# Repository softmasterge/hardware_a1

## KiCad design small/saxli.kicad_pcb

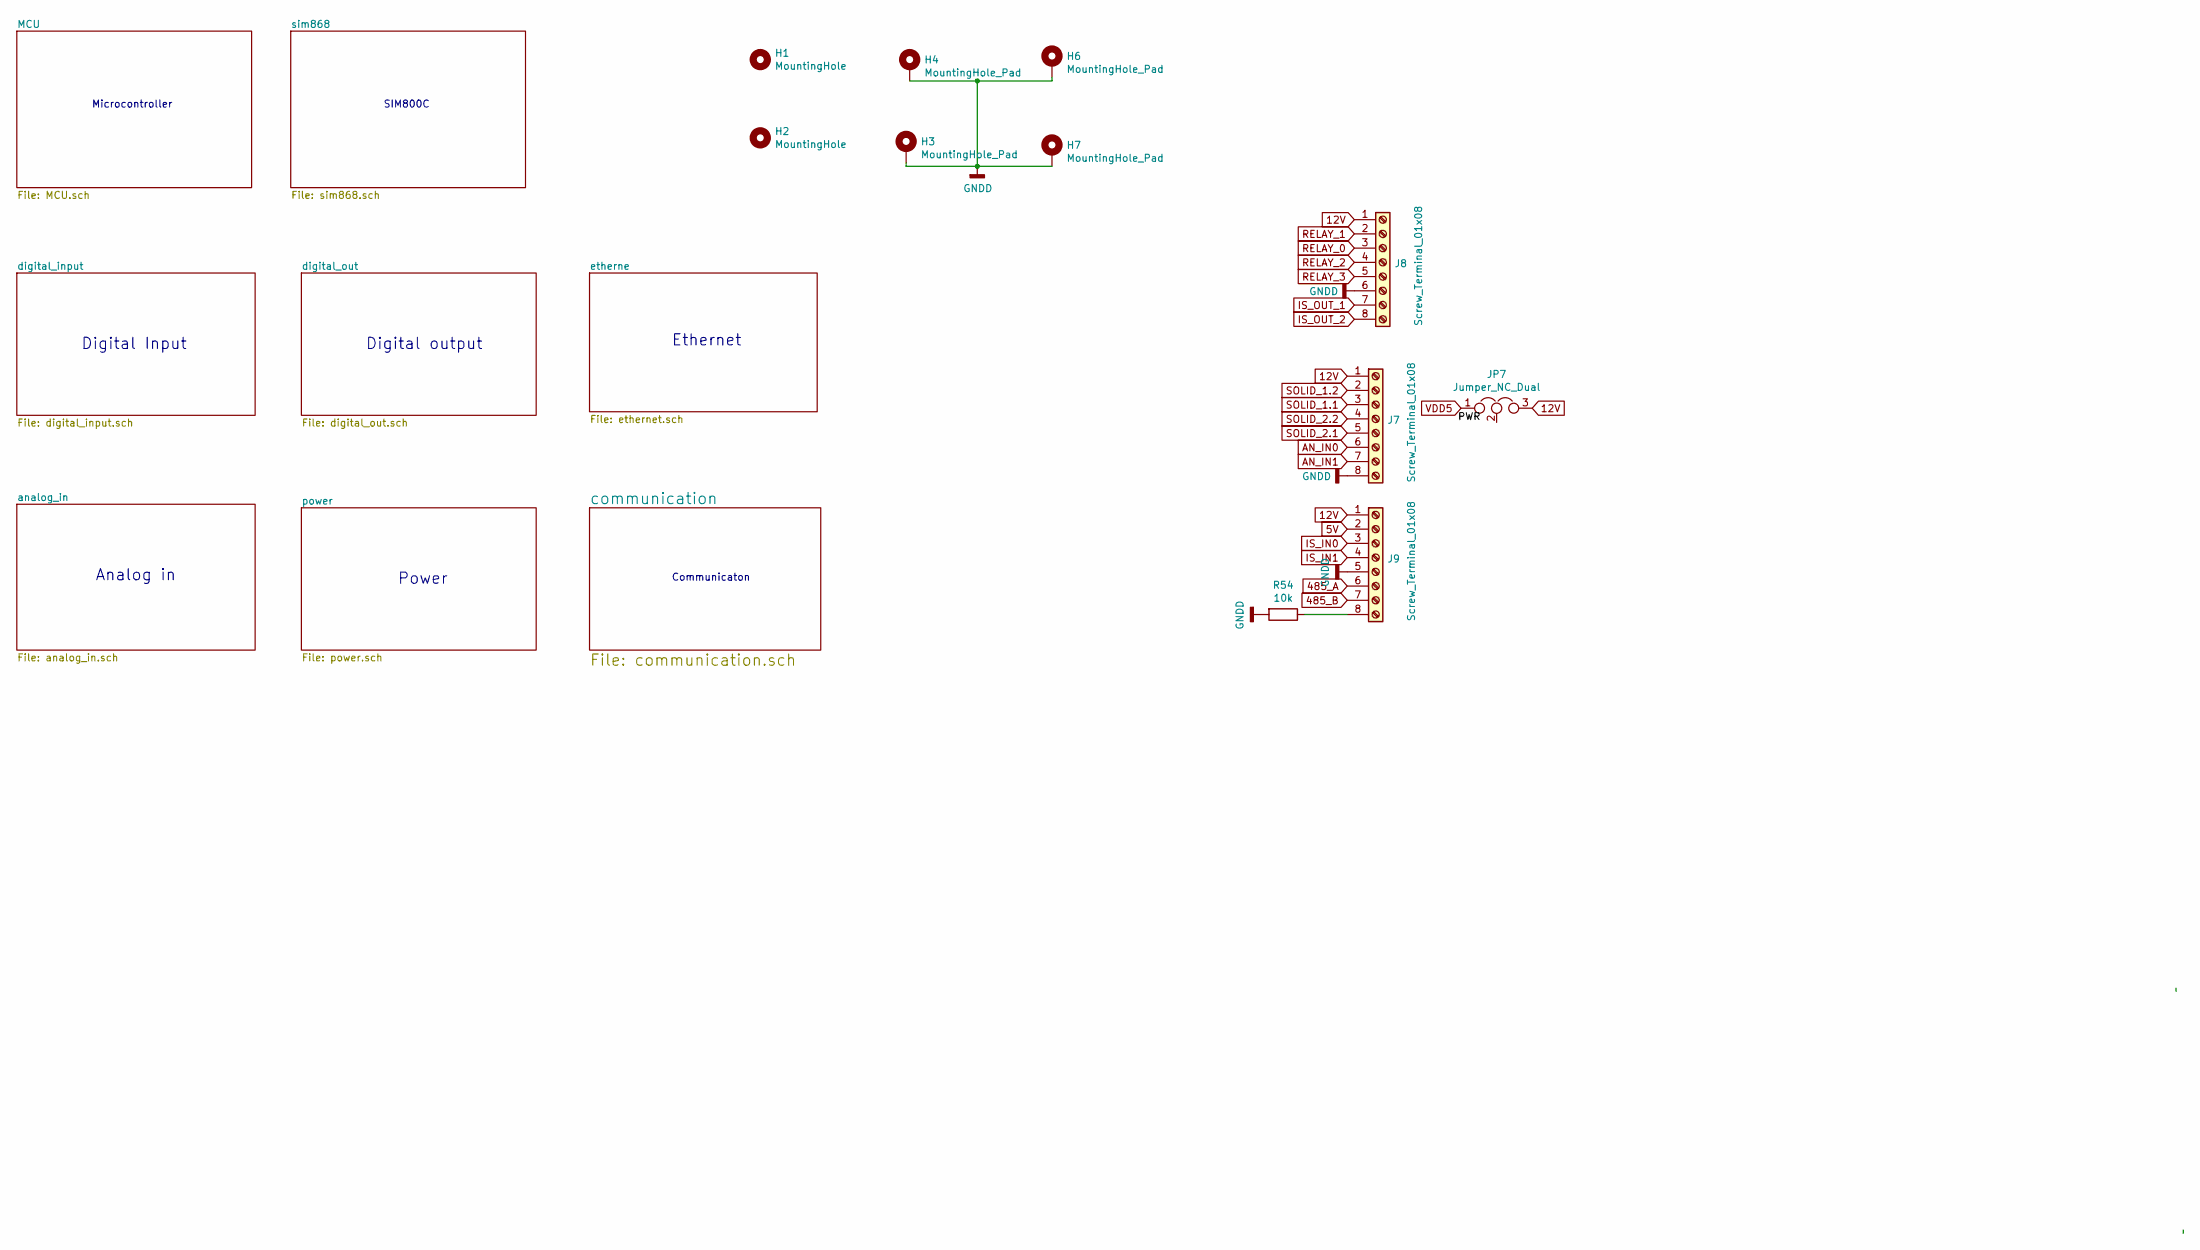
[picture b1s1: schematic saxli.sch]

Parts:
H1, H2: MountingHole; MountingHole_3.2mm_M3; LCSC N/A
H3, H4, H6, H7: MountingHole_Pad; MountingHole_3.2mm_M3_Pad; Mpn #; LCSC N/A
J7, J8, J9: Screw_Terminal_01x08; TerminalBlock_Phoenix_MPT-0,5-8-2.54_1x08_P2.54mm_Horizontal; LCSC N/A
JP7: Jumper_NC_Dual; SolderJumper-3_P1.3mm_Open_Pad1.0x1.5mm; LCSC N/A
R54: 10k; R_0603_1608Metric; MPN 0603WAF1002T5E; LCSC C25804

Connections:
5V: J9.2
485_A: J9.6; also elsewhere on the board
485_B: J9.7; also elsewhere on the board
AN_IN0: J7.6; also elsewhere on the board
AN_IN1: J7.7; also elsewhere on the board
GND: H3.1, H4.1, H6.1, H7.1, J7.8, J8.6, J9.5, R54.2; also elsewhere on the board
IS_IN0: J9.3; also elsewhere on the board
IS_IN1: J9.4; also elsewhere on the board
IS_OUT_1: J8.7; also elsewhere on the board
IS_OUT_2: J8.8; also elsewhere on the board
unnamed: J9.8, R54.1
RELAY_0: J8.3; also elsewhere on the board
RELAY_1: J8.2; also elsewhere on the board
RELAY_2: J8.4; also elsewhere on the board
RELAY_3: J8.5; also elsewhere on the board
SOLID_1.1: J7.3; also elsewhere on the board
SOLID_1.2: J7.2; also elsewhere on the board
SOLID_2.1: J7.5; also elsewhere on the board
SOLID_2.2: J7.4; also elsewhere on the board
VDD5: JP7.1; also elsewhere on the board

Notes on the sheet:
Microcontroller
Digital Input
Digital output
Ethernet
Analog in
Power
Communicaton
SIM800C

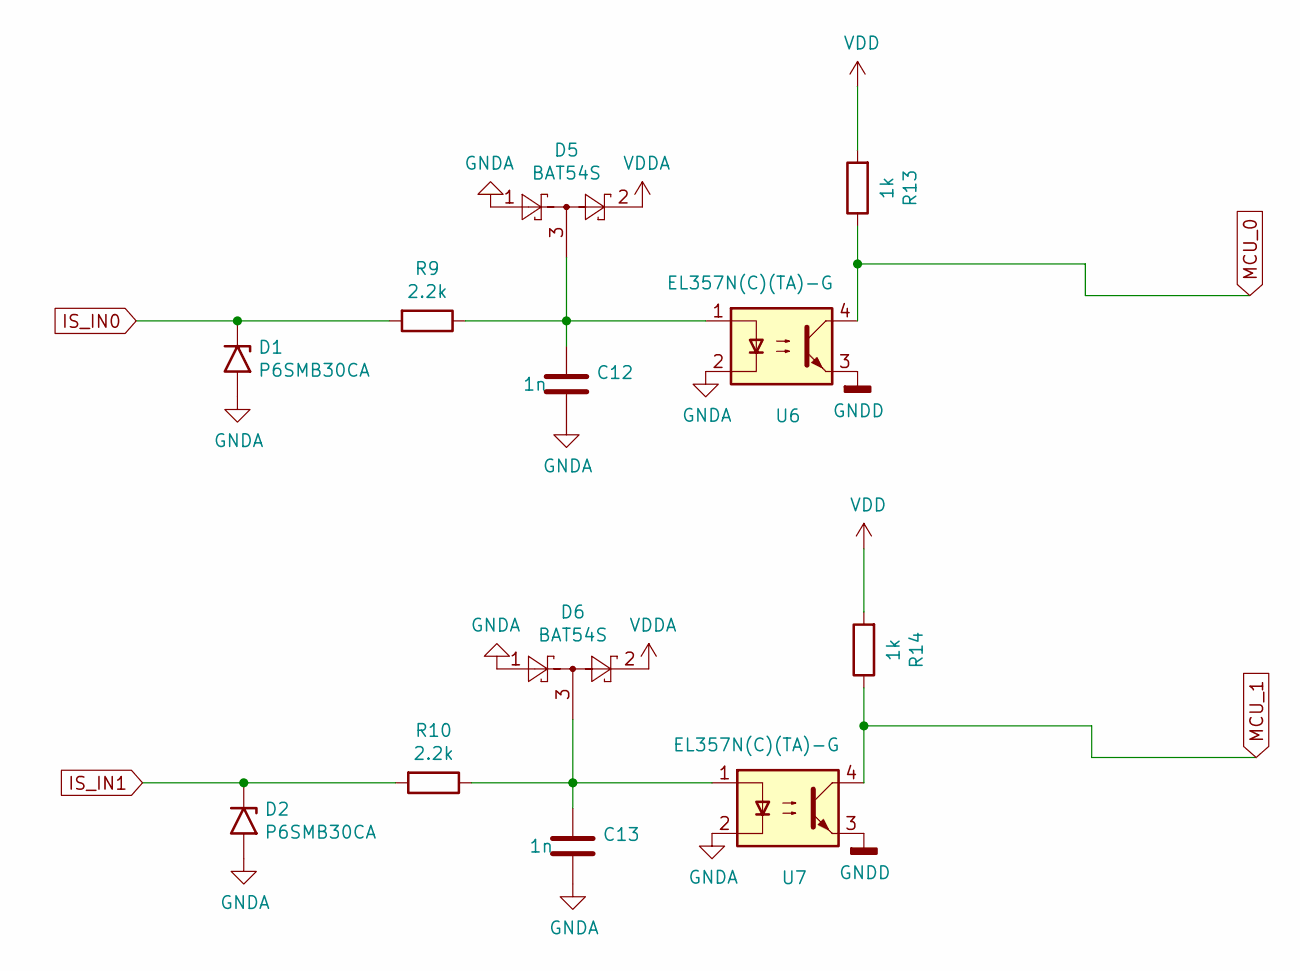
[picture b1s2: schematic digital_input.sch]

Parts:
C12, C13: 1n; C_0603_1608Metric; MPN CL21B102KBCNNNC; LCSC C46653
D1, D2: P6SMB30CA; D_SMB; MPN P6SMB30CA; LCSC C320521
D5, D6: BAT54S; SOT-23; MPN BAT54S L44; LCSC C122856
R9, R10: 2.2k; R_0805_2012Metric; MPN 0805W8F2201T5E; LCSC C17520
R13, R14: 1k; R_0805_2012Metric; MPN 0805W8F1001T5E; LCSC C17513
U6, U7: EL357N(C)(TA)-G; SO-4_4.4x3.6mm_P2.54mm; MPN EL357N(C)(TA)-G; LCSC C29981

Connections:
GND: C12.2, C13.2, D1.2 (A2), D2.2 (A2), D5.1, D6.1, U6.2, U6.3, U7.2, U7.3; also elsewhere on the board
IS_IN0: D1.1 (A1), R9.2; also elsewhere on the board
IS_IN1: D2.1 (A1), R10.2; also elsewhere on the board
MCU_0: R13.1, U6.4; also elsewhere on the board
MCU_1: R14.1, U7.4; also elsewhere on the board
unnamed: C12.1, D5.3, R9.1, U6.1
unnamed: C13.1, D6.3, R10.1, U7.1
VDD3: R13.2, R14.2; also elsewhere on the board
VDDA: D5.2, D6.2; also elsewhere on the board

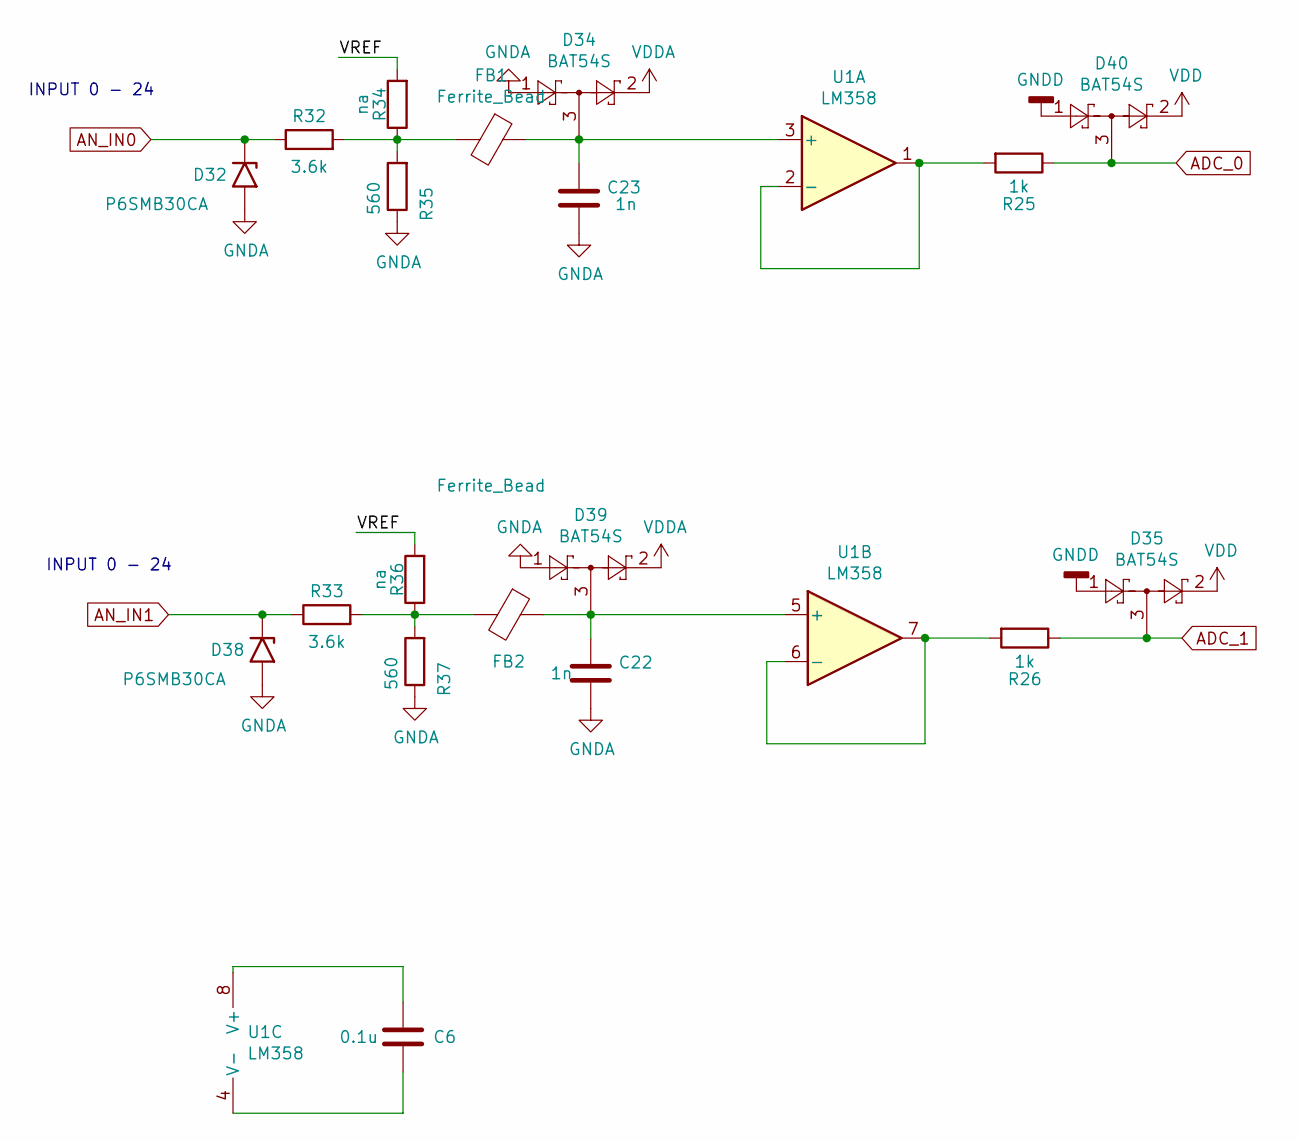
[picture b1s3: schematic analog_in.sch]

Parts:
C6: 0.1u; C_0603_1608Metric; MPN CC0603KRX7R9BB104; LCSC C14663
C22, C23: 1n; C_0603_1608Metric; MPN CL21B102KBCNNNC; LCSC C46653
D32, D38: P6SMB30CA; D_SMB; MPN P6SMB30CA; LCSC C320521
D34, D35, D39, D40: BAT54S; SOT-23; MPN BAT54S L44; LCSC C122856
FB1, FB2: Ferrite_Bead; R_0805_2012Metric_Pad1.20x1.40mm_HandSolder; MPN GZ2012D601TF; LCSC C1017
R25, R26: 1k; R_0603_1608Metric; MPN 0603WAF1001T5E; LCSC C21190
R32, R33: 3.6k; R_0805_2012Metric; MPN 0805W8F3601T5E; LCSC C18359
R34, R36: na; R_0603_1608Metric; LCSC N/A
R35, R37: 560; R_0805_2012Metric; MPN 0805W8F5600T5E; LCSC C28636
U1: LM358; SOIC-8_3.9x4.9mm_P1.27mm; LCSC C7950

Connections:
/analog_in/VREF: R34.2, R36.2
ADC_0: D40.3, R25.1; also elsewhere on the board
ADC_1: D35.3, R26.1; also elsewhere on the board
AN_IN0: D32.1 (A1), R32.1; also elsewhere on the board
AN_IN1: D38.1 (A1), R33.1; also elsewhere on the board
GND: C22.2, C23.2, D32.2 (A2), D34.1, D35.1, D38.2 (A2), D39.1, D40.1, R35.1, R37.1; also elsewhere on the board
unnamed: C6.1, U1.8 (V+)
unnamed: C6.2, U1.4 (V-)
unnamed: C22.1, D39.3, FB2.1, U1.5 (+)
unnamed: C23.1, D34.3, FB1.1, U1.3 (+)
unnamed: FB1.2, R32.2, R34.1, R35.2
unnamed: FB2.2, R33.2, R36.1, R37.2
unnamed: R25.2, U1.1, U1.2 (-)
unnamed: R26.2, U1.6 (-), U1.7
VDD3: D35.2, D40.2; also elsewhere on the board
VDDA: D34.2, D39.2; also elsewhere on the board

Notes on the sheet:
INPUT 0 - 24

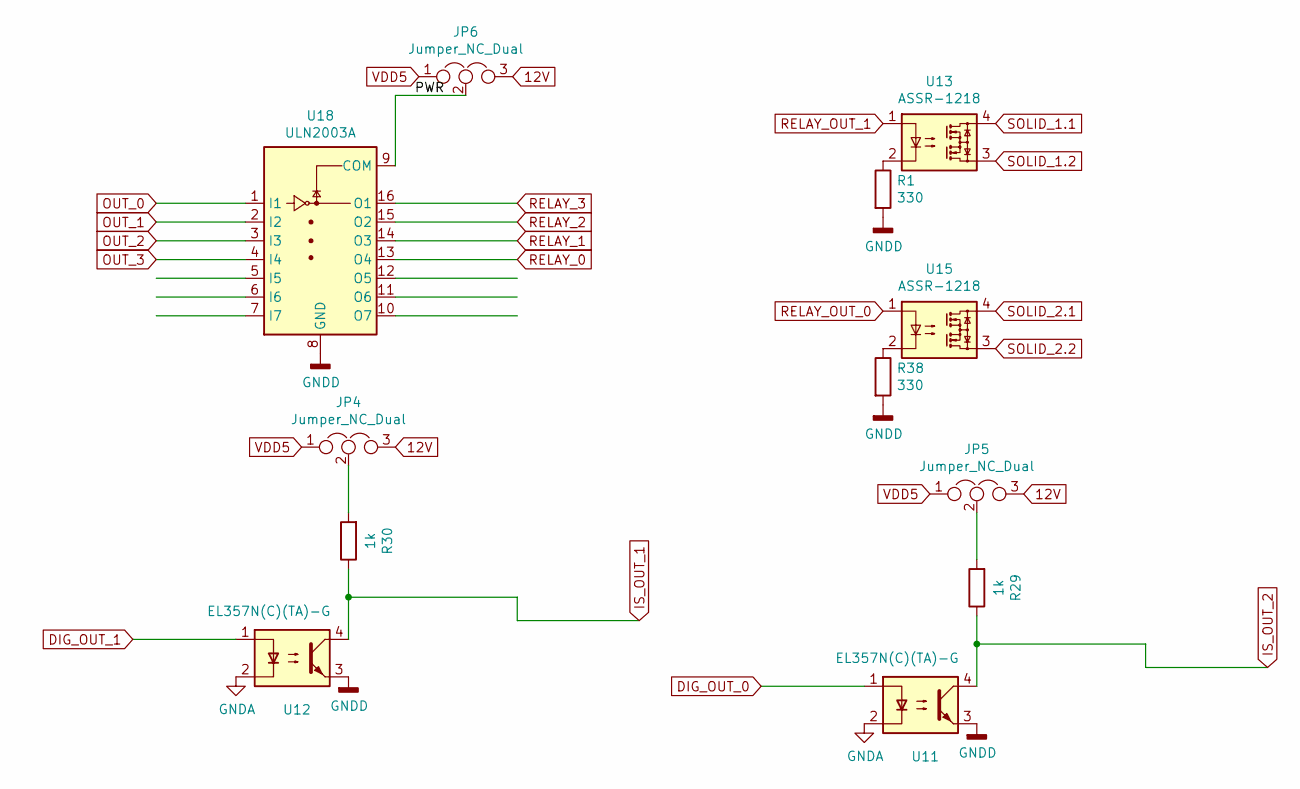
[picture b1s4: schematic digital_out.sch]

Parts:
JP4, JP5, JP6: Jumper_NC_Dual; SolderJumper-3_P1.3mm_Open_Pad1.0x1.5mm; LCSC N/A
R1, R38: 330; R_0603_1608Metric; MPN 0603WAF3300T5E; LCSC C23138
R29, R30: 1k; R_0805_2012Metric; MPN 0805W8F1001T5E; LCSC C17513
U11, U12: EL357N(C)(TA)-G; SO-4_4.4x3.6mm_P2.54mm; MPN EL357N(C)(TA)-G; LCSC C29981
U13, U15: ASSR-1218; SMDIP-4_W7.62mm; MPN AQY211EHAX; LCSC C129282
U18: ULN2003A; SOIC-16_3.9x9.9mm_P1.27mm; MPN ULN2003ADR; LCSC C7512

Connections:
/digital_out/PWR: JP6.2, U18.9 (COM)
DIG_OUT_0: U11.1; also elsewhere on the board
DIG_OUT_1: U12.1; also elsewhere on the board
GND: R1.2, R38.2, U11.2, U11.3, U12.2, U12.3, U18.8 (GND); also elsewhere on the board
IS_OUT_1: R30.1, U12.4; also elsewhere on the board
IS_OUT_2: R29.1, U11.4; also elsewhere on the board
unnamed: JP4.2, R30.2
unnamed: JP5.2, R29.2
unnamed: R1.1, U13.2
unnamed: R38.1, U15.2
OUT_0: U18.1 (I1); also elsewhere on the board
OUT_1: U18.2 (I2); also elsewhere on the board
OUT_2: U18.3 (I3); also elsewhere on the board
OUT_3: U18.4 (I4); also elsewhere on the board
RELAY_0: U18.13 (O4); also elsewhere on the board
RELAY_1: U18.14 (O3); also elsewhere on the board
RELAY_2: U18.15 (O2); also elsewhere on the board
RELAY_3: U18.16 (O1); also elsewhere on the board
RELAY_OUT_0: U15.1; also elsewhere on the board
RELAY_OUT_1: U13.1; also elsewhere on the board
SOLID_1.1: U13.4; also elsewhere on the board
SOLID_1.2: U13.3; also elsewhere on the board
SOLID_2.1: U15.4; also elsewhere on the board
SOLID_2.2: U15.3; also elsewhere on the board
VDD5: JP4.1, JP5.1, JP6.1; also elsewhere on the board

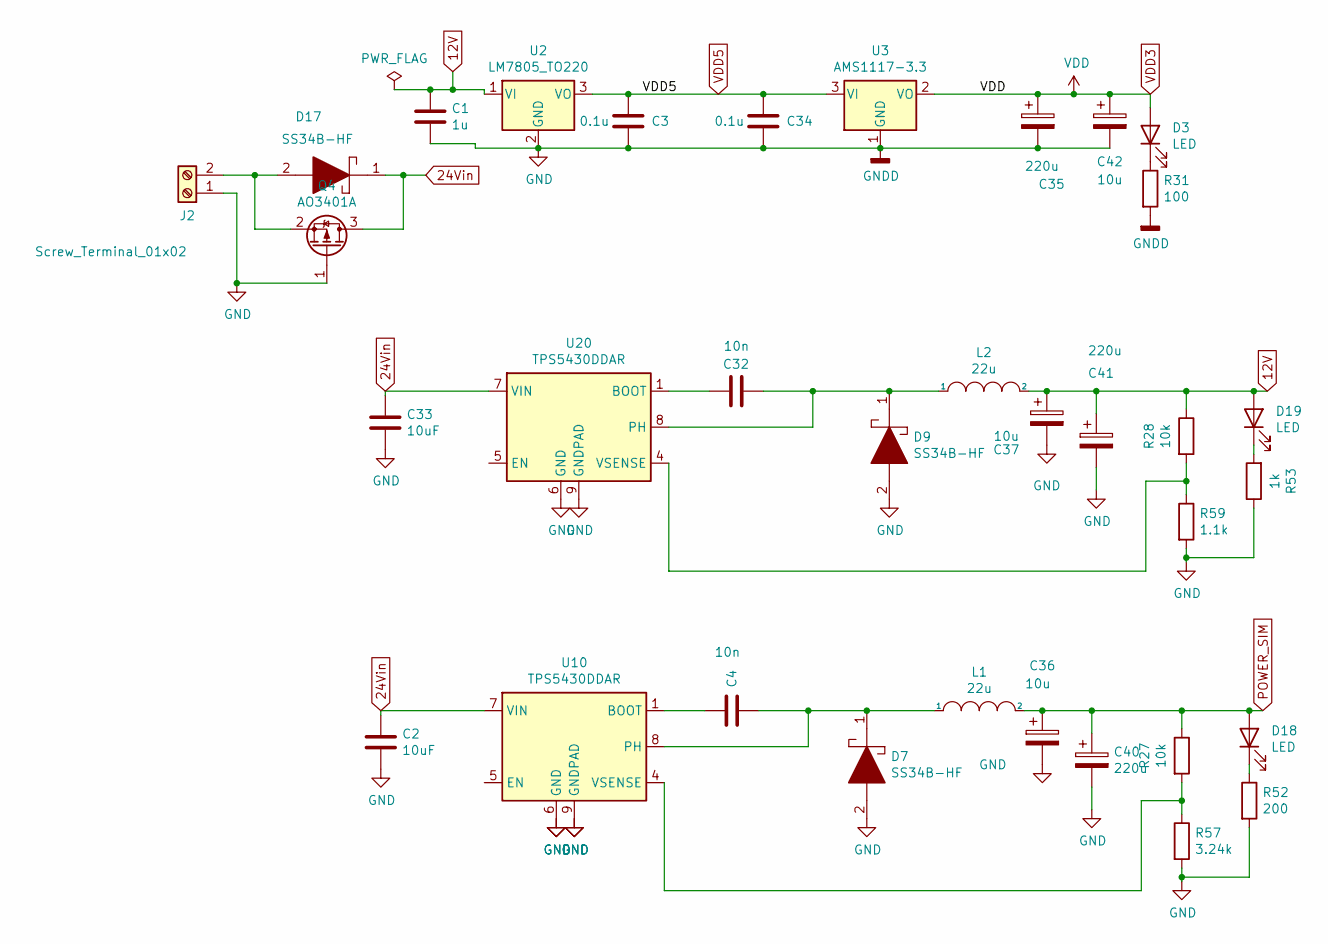
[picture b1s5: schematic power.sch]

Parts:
C1: 1u; R_0805_2012Metric; MPN CL21B105KBFNNNE; LCSC C28323
C2, C33: 10uF; C_1206_3216Metric; MPN CL31A106KBHNNNE; LCSC C13585
C3, C34: 0.1u; C_0603_1608Metric; MPN CC0603KRX7R9BB104; LCSC C14663
C4, C32: 10n; R_0603_1608Metric; MPN 0603B103K500NT; LCSC C57112
C35, C40, C41: 220u; CP_Elec_8x10; MPN VEH221M1VTR; LCSC C311611
C36, C37, C42: 10u; CP_EIA-3216-18_Kemet-A; MPN TAJA106K016RNJ; LCSC C7171
D3: LED; LED_0805_2012Metric; MPN FC-2012HRK-620D; LCSC C84256
D7, D9, D17: SS34B-HF; DIOM5336X320N; Mouser Part Number 750-SS34B-HF
D18, D19: LED; LED_0805_2012Metric_Pad1.15x1.40mm_HandSolder; MPN ORH-YG35A; LCSC C205449
J2: Screw_Terminal_01x02; TerminalBlock_Phoenix_MKDS-1,5-2-5.08_1x02_P5.08mm_Horizont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; Mpn Connector unknown; LCSC N/A
L1, L2: 22u; L_10.4x10.4_H4.8; MPN SLO1040H220MTT; LCSC C182173
Q4: AO3401A; SOT-23; MPN AO3401A; LCSC C15127
R27, R28: 10k; R_0603_1608Metric; MPN 0603WAF1002T5E; LCSC C25804
R31: 100; R_0603_1608Metric; MPN 0603WAF1000T5E; LCSC C22775
R52: 200; R_0603_1608Metric; MPN 0603WAF2000T5E; LCSC C8218
R53: 1k; R_0805_2012Metric; MPN 0805W8F1001T5E; LCSC C17513
R57: 3.24k; R_0603_1608Metric; MPN 0603WAF3241T5E; LCSC C22994
R59: 1.1k; R_0603_1608Metric; MPN 0603WAF1101T5E; LCSC C22764
U2: LM7805_TO220; TO-252-2; MPN CJ7805; LCSC C21706
U3: AMS1117-3.3; SOT-223; MPN AMS1117-3.3; LCSC C6186
U10, U20: TPS5430DDAR; TI_SO-PowerPAD-8_ThermalVias; MPN TPS5430DDAR; LCSC C9864

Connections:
24Vin: C2.1, C33.1, D17.1, Q4.3 (D), U10.7 (VIN), U20.7 (VIN)
GND: C1.2, C2.2, C3.2, C33.2, C34.2, C35.2, C36.2, C37.2, C40.2, C41.2, C42.2, D7.2, D9.2, J2.1, Q4.1 (G), R31.2, R52.2, R53.1, R57.2, R59.2, U2.2 (GND), U3.1 (GND), U10.6 (GND), U10.9 (GNDPAD), U20.6 (GND), U20.9 (GNDPAD); also elsewhere on the board
unnamed: C4.1, U10.1 (BOOT)
unnamed: C4.2, D7.1, L1.1, U10.8 (PH)
unnamed: C32.1, U20.1 (BOOT)
unnamed: C32.2, D9.1, L2.1, U20.8 (PH)
unnamed 72: C36.1, C40.1, D18.2 (A), L1.2, R27.1; also elsewhere on the board
unnamed: D3.1 (K), R31.1
unnamed: D17.2, J2.2, Q4.2 (S)
unnamed: D18.1 (K), R52.1
unnamed: D19.1 (K), R53.2
unnamed: R27.2, R57.1, U10.4 (VSENSE)
unnamed: R28.2, R59.1, U20.4 (VSENSE)
VDD3: C35.1, C42.1, D3.2 (A), U3.2 (VO); also elsewhere on the board
VDD5: C3.1, C34.1, U2.3 (VO), U3.3 (VI); also elsewhere on the board

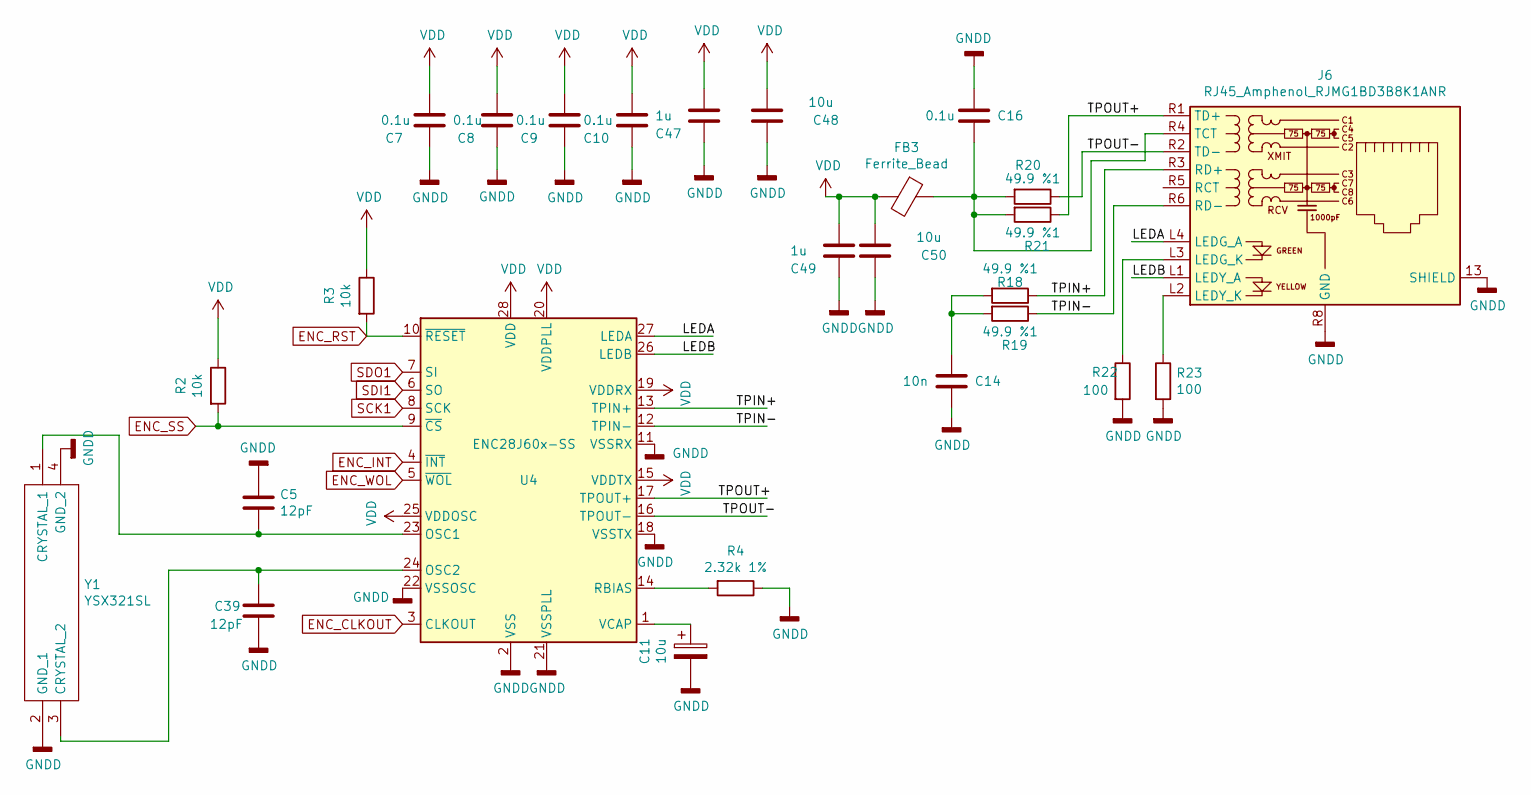
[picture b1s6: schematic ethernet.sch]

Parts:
C5, C39: 12pF; C_0603_1608Metric; MPN CL10C120JB8NNNC; LCSC C38523
C7, C8, C9, C10, C16: 0.1u; C_0603_1608Metric; MPN CC0603KRX7R9BB104; LCSC C14663
C11: 10u; CP_EIA-3216-18_Kemet-A; MPN TAJA106K016RNJ; LCSC C7171
C14: 10n; C_0603_1608Metric; MPN 0603B103K500NT; LCSC C57112
C47, C49: 1u; C_0603_1608Metric; MPN CL10A105KB8NNNC; LCSC C15849
C48, C50: 10u; C_0603_1608Metric; MPN GRM188R61E106KA73D; LCSC C344022
FB3: Ferrite_Bead; R_0805_2012Metric_Pad1.20x1.40mm_HandSolder; MPN GZ2012D601TF; LCSC C1017
J6: RJ45_Amphenol_RJMG1BD3B8K1ANR; LCSC N/A
R2, R3: 10k; R_0603_1608Metric; MPN 0603WAF1002T5E; LCSC C25804
R4: 2.32k 1%; R_0603_1608Metric; MPN 0603WAF2321T5E; LCSC C22905
R18, R19, R20, R21: 49.9 %1; R_0603_1608Metric; MPN 0603WAF499JT5E; LCSC C23185
R22, R23: 100; R_0603_1608Metric; MPN 0603WAF1005T5E; LCSC C7250
U4: ENC28J60x-SS; SOIC-28W_7.5x17.9mm_P1.27mm; LCSC C47351
Y1: YSX321SL; Manufacturer_Part_Number YSX321SL; LCSC C9006

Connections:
/etherne/LEDA: J6.L4 (LEDG_A), U4.27 (LEDA)
/etherne/LEDB: J6.L1 (LEDY_A), U4.26 (LEDB)
/etherne/TPIN+: J6.R3 (RD+), R18.1, U4.13 (TPIN+)
/etherne/TPIN-: J6.R6 (RD-), R19.1, U4.12 (TPIN-)
/etherne/TPOUT+: J6.R1 (TD+), R21.1, U4.17 (TPOUT+)
/etherne/TPOUT-: J6.R2 (TD-), R20.1, U4.16 (TPOUT-)
ENC_CLKOUT: U4.3 (CLKOUT)
ENC_INT: U4.4 (~INT); also elsewhere on the board
ENC_RST: R3.2, U4.10 (~RESET); also elsewhere on the board
ENC_SS: R2.2, U4.9 (~CS); also elsewhere on the board
ENC_WOL: U4.5 (~WOL); also elsewhere on the board
GND: C5.1, C7.2, C8.2, C9.2, C10.2, C11.2, C14.2, C16.1, C39.2, C47.2, C48.2, C49.2, C50.2, J6.13 (SHIELD), J6.R8 (GND), R4.1, R22.2, R23.2, U4.2 (VSS), U4.11 (VSSRX), U4.18 (VSSTX), U4.21 (VSSPLL), U4.22 (VSSOSC), Y1.2 (GND_1), Y1.4 (GND_2); also elsewhere on the board
unnamed: C5.2, U4.23 (OSC1), Y1.1 (CRYSTAL_1)
unnamed: C11.1, U4.1 (VCAP)
unnamed: C14.1, R18.2, R19.2
unnamed: C16.2, FB3.1, J6.R4 (TCT), R20.2, R21.2
unnamed: C39.1, U4.24 (OSC2), Y1.3 (CRYSTAL_2)
unnamed: J6.L2 (LEDY_K), R23.1
unnamed: J6.L3 (LEDG_K), R22.1
unnamed: R4.2, U4.14 (RBIAS)
SCK1: U4.8 (SCK); also elsewhere on the board
SDI1: U4.6 (SO); also elsewhere on the board
SDO1: U4.7 (SI); also elsewhere on the board
VDD3: C7.1, C8.1, C9.1, C10.1, C47.1, C48.1, C49.1, C50.1, FB3.2, R2.1, R3.1, U4.15 (VDDTX), U4.19 (VDDRX), U4.20 (VDDPLL), U4.25 (VDDOSC), U4.28 (VDD); also elsewhere on the board

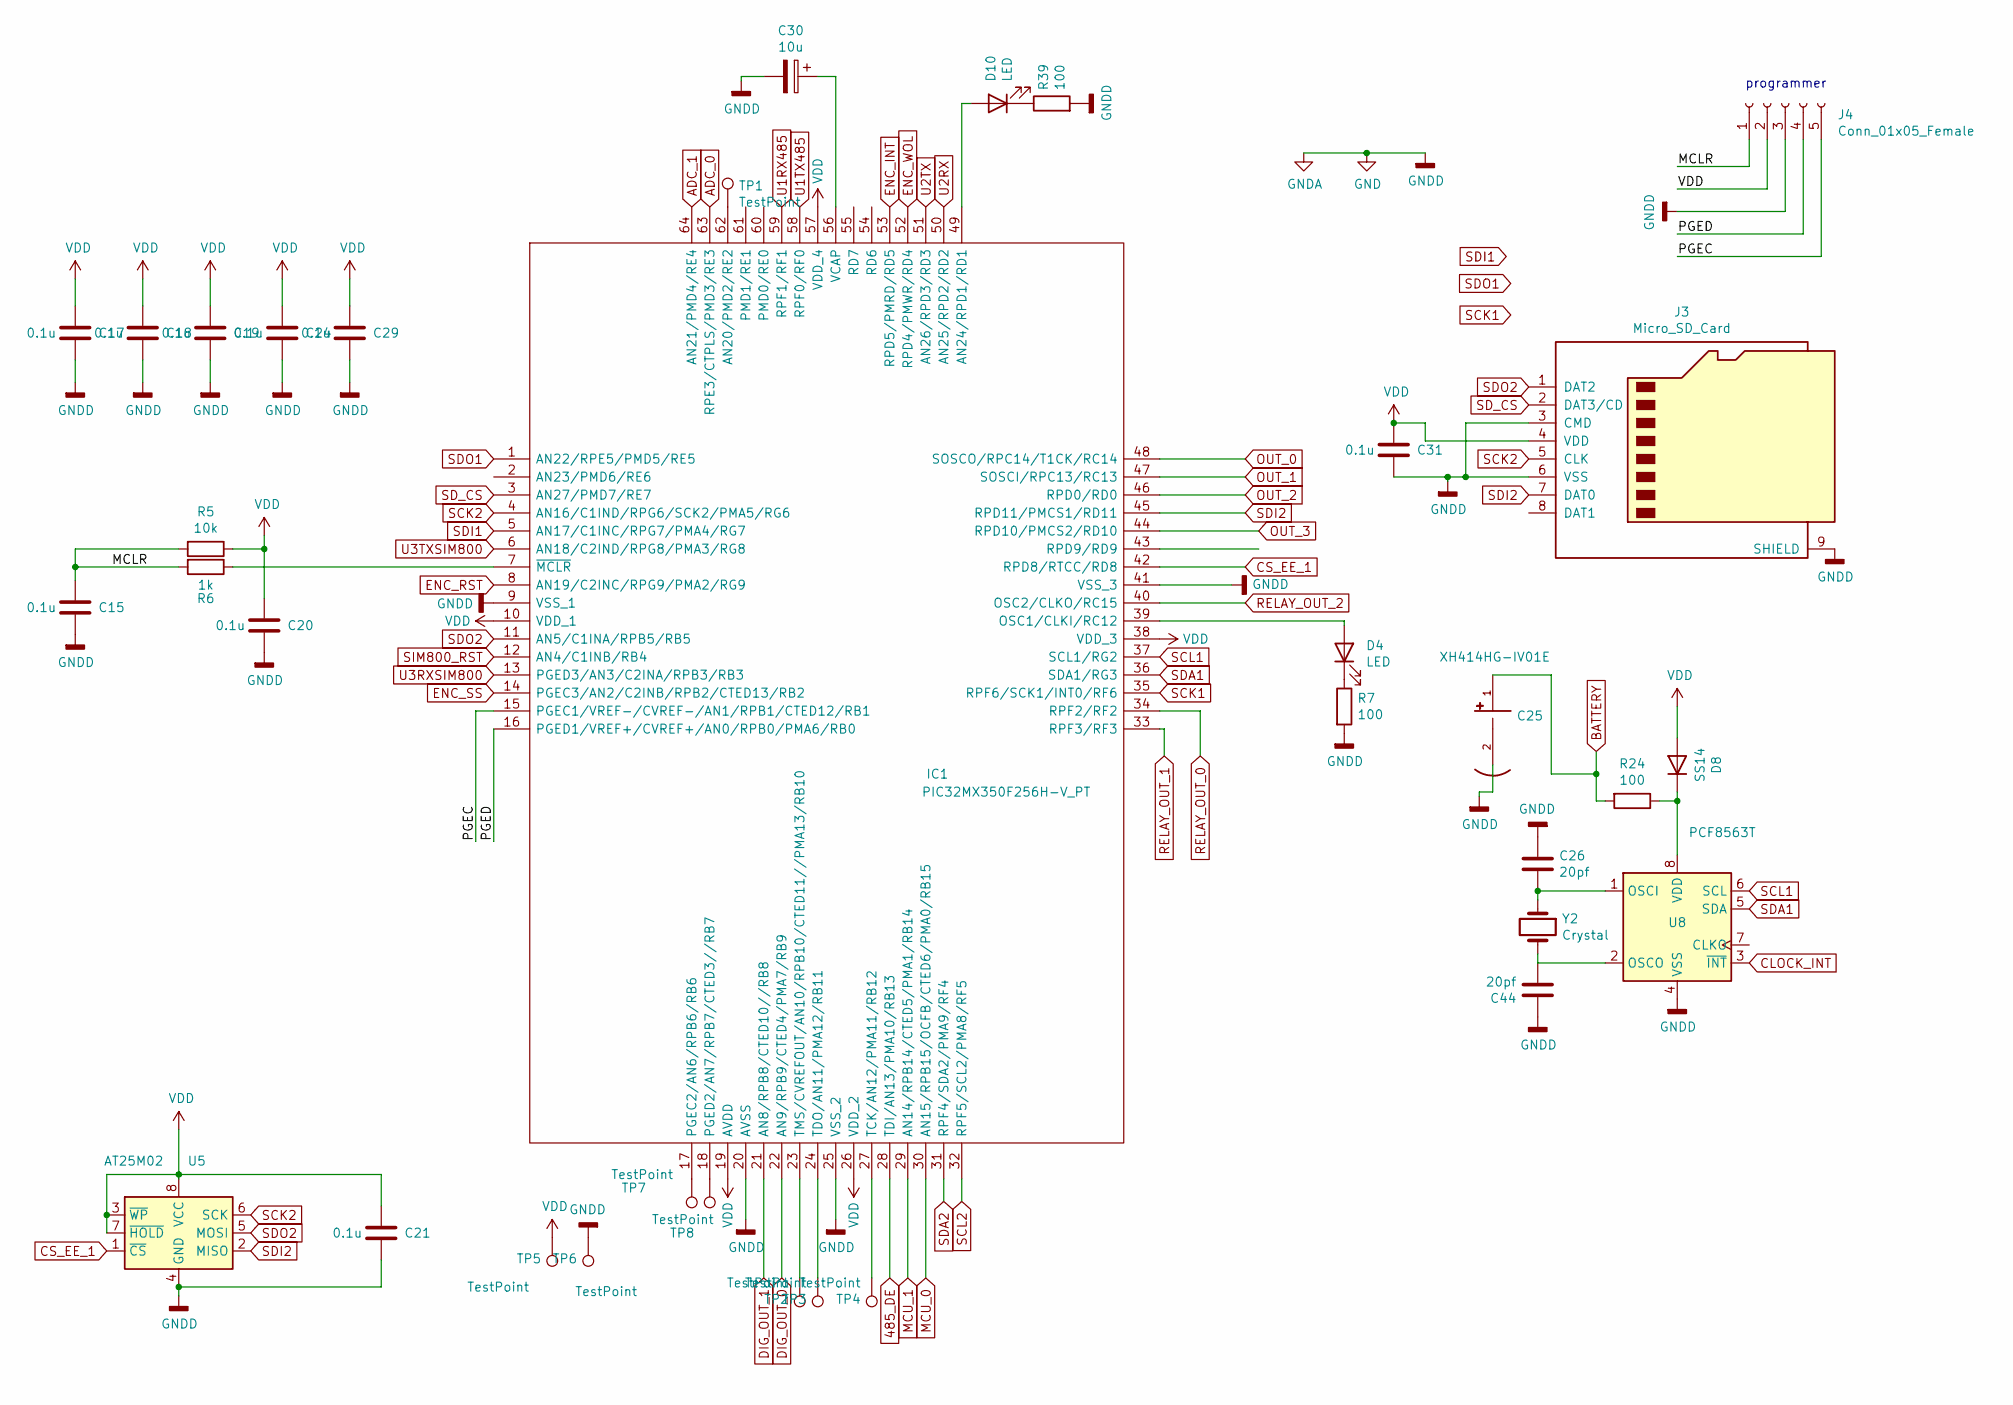
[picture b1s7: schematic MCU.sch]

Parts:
C15, C17, C18, C19, C20, C21, C24, C29, C31: 0.1u; C_0603_1608Metric; MPN CC0603KRX7R9BB104; LCSC C14663
C25: XH414HG-IV01E; CAP_XH414HG-IV01E; MPN XH414HG-IV01E; LCSC C38065
C26, C44: 20pf; C_0603_1608Metric_Pad1.08x0.95mm_HandSolder; MPN CL10C200JB8NNNC; LCSC C1648
C30: 10u; CP_EIA-3216-18_Kemet-A; MPN TAJA106K016RNJ; LCSC C7171
D4, D10: LED; LED_0805_2012Metric; MPN FC-2012HRK-620D; LCSC C84256
D8: SS14; D_SMA; MPN SS14; LCSC C2480
IC1: PIC32MX350F256H-V_PT; QFP50P1200X1200X120-64N; Mouser Part Number 579-32MX350F256HVPT
J3: Micro_SD_Card; microSD_HC_Hirose_DM3BT-DSF-PEJS; LCSC N/A
J4: Conn_01x05_Female; PinHeader_1x05_P2.54mm_Vertical; Mpn Connector unknown; LCSC N/A
R5: 10k; R_0603_1608Metric; MPN 0603WAF1002T5E; LCSC C25804
R6: 1k; R_0603_1608Metric; MPN 0603WAF1001T5E; LCSC C21190
R7, R39: 100; R_0603_1608Metric; MPN 0603WAF1000T5E; LCSC C22775
R24: 100; R_0603_1608Metric; MPN 0603WAF1005T5E; LCSC C7250
TP1, TP2, TP3, TP4, TP5, TP6, TP7, TP8: TestPoint; TestPoint_Pad_1.5x1.5mm; LCSC N/A
U5: AT25M02; SOIC-8_3.9x4.9mm_P1.27mm; MPN AT25M02-SSHD-T; LCSC N/A
U8: PCF8563T; SOIC-8_3.9x4.9mm_P1.27mm; MPN PCF8563T; LCSC C7440
Y2: Crystal; Crystal_SMD_3215-2Pin_3.2x1.5mm; MPN Q13FC1350000400; LCSC C32346

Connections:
485_DE: IC1.28 (TDI/AN13/PMA10/RB13); also elsewhere on the board
/MCU/MCLR: C15.1, J4.1, R5.2, R6.2
/MCU/PGEC: IC1.15 (PGEC1/VREF-/CVREF-/AN1/RPB1/CTED12/RB1), J4.5
/MCU/PGED: IC1.16 (PGED1/VREF+/CVREF+/AN0/RPB0/PMA6/RB0), J4.4
ADC_0: IC1.63 (RPE3/CTPLS/PMD3/RE3); also elsewhere on the board
ADC_1: IC1.64 (AN21/PMD4/RE4); also elsewhere on the board
BATTERY: C25.1, R24.2
CLOCK_INT: U8.3 (~INT~)
CS_EE_1: IC1.42 (RPD8/RTCC/RD8), U5.1 (~CS)
DIG_OUT_0: IC1.22 (AN9/RPB9/CTED4/PMA7/RB9); also elsewhere on the board
DIG_OUT_1: IC1.21 (AN8/RPB8/CTED10//RB8); also elsewhere on the board
ENC_INT: IC1.53 (RPD5/PMRD/RD5); also elsewhere on the board
ENC_RST: IC1.8 (AN19/C2INC/RPG9/PMA2/RG9); also elsewhere on the board
ENC_SS: IC1.14 (PGEC3/AN2/C2INB/RPB2/CTED13/RB2); also elsewhere on the board
ENC_WOL: IC1.52 (RPD4/PMWR/RD4); also elsewhere on the board
GND: C15.2, C17.2, C18.2, C19.2, C20.2, C21.2, C24.2, C25.2, C26.1, C29.2, C30.2, C31.2, C44.1, IC1.9 (VSS_1), IC1.20 (AVSS), IC1.25 (VSS_2), IC1.41 (VSS_3), J3.3 (CMD), J3.6 (VSS), J3.9 (SHIELD), J4.3, R7.2, R39.2, TP6.1, U5.4 (GND), U8.4 (VSS); also elsewhere on the board
MCU_0: IC1.30 (AN15/RPB15/OCFB/CTED6/PMA0/RB15); also elsewhere on the board
MCU_1: IC1.29 (AN14/RPB14/CTED5/PMA1/RB14); also elsewhere on the board
unnamed: C26.2, U8.1 (OSCI), Y2.1
unnamed: C30.1, IC1.56 (VCAP)
unnamed: C44.2, U8.2 (OSCO), Y2.2
unnamed 75: D8.2 (K), R24.1, U8.8 (VDD); also elsewhere on the board
unnamed: D4.1 (K), R7.1
unnamed: D4.2 (A), IC1.39 (OSC1/CLKI/RC12)
unnamed: D10.1 (K), R39.1
unnamed: D10.2 (A), IC1.49 (AN24/RPD1/RD1)
unnamed: IC1.7 (~MCLR), R6.1
unnamed: IC1.17 (PGEC2/AN6/RPB6/RB6), TP7.1
unnamed: IC1.18 (PGED2/AN7/RPB7/CTED3//RB7), TP8.1
unnamed: IC1.23 (TMS/CVREFOUT/AN10/RPB10/CTED11//PMA13/R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), TP2.1
unnamed: IC1.24 (TDO/AN11/PMA12/RB11), TP3.1
unnamed: IC1.27 (TCK/AN12/PMA11/RB12), TP4.1
unnamed: IC1.62 (AN20/PMD2/RE2), TP1.1
OUT_0: IC1.48 (SOSCO/RPC14/T1CK/RC14); also elsewhere on the board
OUT_1: IC1.47 (SOSCI/RPC13/RC13); also elsewhere on the board
OUT_2: IC1.46 (RPD0/RD0); also elsewhere on the board
OUT_3: IC1.44 (RPD10/PMCS2/RD10); also elsewhere on the board
RELAY_OUT_0: IC1.34 (RPF2/RF2); also elsewhere on the board
RELAY_OUT_1: IC1.33 (RPF3/RF3); also elsewhere on the board
RELAY_OUT_2: IC1.40 (OSC2/CLKO/RC15)
SCK1: IC1.35 (RPF6/SCK1/INT0/RF6); also elsewhere on the board
SCK2: IC1.4 (AN16/C1IND/RPG6/SCK2/PMA5/RG6), J3.5 (CLK), U5.6 (SCK)
SCL1: IC1.37 (SCL1/RG2), U8.6 (SCL); also elsewhere on the board
SCL2: IC1.32 (RPF5/SCL2/PMA8/RF5); also elsewhere on the board
SDA1: IC1.36 (SDA1/RG3), U8.5 (SDA); also elsewhere on the board
SDA2: IC1.31 (RPF4/SDA2/PMA9/RF4); also elsewhere on the board
SDI1: IC1.5 (AN17/C1INC/RPG7/PMA4/RG7); also elsewhere on the board
SDI2: IC1.45 (RPD11/PMCS1/RD11), J3.7 (DAT0), U5.2 (MISO)
SDO1: IC1.1 (AN22/RPE5/PMD5/RE5); also elsewhere on the board
SDO2: IC1.11 (AN5/C1INA/RPB5/RB5), J3.1 (DAT2), U5.5 (MOSI)
SD_CS: IC1.3 (AN27/PMD7/RE7), J3.2 (DAT3/CD)
SIM800_RST: IC1.12 (AN4/C1INB/RB4); also elsewhere on the board
U1RX485: IC1.59 (RPF1/RF1); also elsewhere on the board
U1TX485: IC1.58 (RPF0/RF0); also elsewhere on the board
U2RX: IC1.50 (AN25/RPD2/RD2); also elsewhere on the board
U2TX: IC1.51 (AN26/RPD3/RD3); also elsewhere on the board
U3RXSIM800: IC1.13 (PGED3/AN3/C2INA/RPB3/RB3); also elsewhere on the board
U3TXSIM800: IC1.6 (AN18/C2IND/RPG8/PMA3/RG8); also elsewhere on the board
VDD3: C17.1, C18.1, C19.1, C20.1, C21.1, C24.1, C29.1, C31.1, D8.1 (A), IC1.10 (VDD_1), IC1.19 (AVDD), IC1.26 (VDD_2), IC1.38 (VDD_3), IC1.57 (VDD_4), J3.4 (VDD), J4.2, R5.1, TP5.1, U5.3 (~WP), U5.7 (~HOLD), U5.8 (VCC); also elsewhere on the board

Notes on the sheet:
programmer
